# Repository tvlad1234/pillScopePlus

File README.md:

# pillScope Plus
Oscilloscope based around the STM32F401 Black Pill and a color LCD screen, meant to be used as an educational tool

## Why does it exist?
The goal of this project was to create a simple and easy to build but still very usable oscillsocope. I wanted to learn the basics of how a **digital storage oscilloscope** functions, while also ending up with something which can be used as an educational tool in the lab. A short description of how oscillscopes (and this one in particular) work can be found [here](HowItWorks.md).

## Features
* -3.3V to 3.3V input range (can be increased if using attenuator probes)
* 1MOhm input impedance
* 10uS/div minimum timebase
* 1.6 MSa/S sampling rate
* On screen measurements:
  * min/max voltage
  * peak-to-peak voltage
  * frequency
* Captured waveforms can be sent to a computer over UART and analyzed in the Tektronix TekScope app
## Required parts
### Base parts:
* STM32F401CC Black Pill development board
* 128x160 ST7735-based TFT display
* 3 pushbuttons
* LM358 dual op-amp (rail-to-rail opamps should work better in this context, but this is what I had on hand)
* 2x 68kOhm resistors (to create a 1.65V offset voltage)
* 2x 500kOhm resistors (to create the input attenuator)

### Useful, but not mandatory:
* a 5V power supply
* an opto-isolated USB UART adapter
* a BNC connector, for using proper oscilloscope probes

## Schematics
The LCD screen is connected to SPI1 (PB3-SCK, PB5-MOSI, PB12-CS, PB13-RST, PB14-DC). The buttons are connected as follows:
* PB9: Up
* PB8: Select
* PB7: Down

The output of the analog frontend is connected to ADC1_IN0, which corresponds to PA0.\
The schematic of the frontend can be found in the [frontend.pdf](frontend.pdf) file.

## Using the oscilloscope
### The UI
The Select button cycles through the different parameters, which can be adjusted using the Up and Down buttons. 

### Auto calibration
Pressing Up and Down at the same time triggers the auto-calibration function. The tip and ground clip of the probed should be coupled together while calibrating. 

### Measuring things
The frontend of the instrument makes use of a virtual ground point which is 1.65V above the real ground. Because of this, the oscilloscope and the device under test must not be sharing the same ground reference. If you need to send data to the computer while measuring a device which shares ground with the scope, you should connect the computer via an opto-isolated adapter, while powering the oscilloscope from an external source.

### Saving captured waveforms
The captured waveforms can be sent to a computer over UART.

#### CSV Output
Sending `s` (lowercase s) to the UART tells the instrument to output the captured waveform in CSV format, which is compatible with the Tektronix TekScope app.

#### Direct TekScope output 
Sending `S` (capital S) tells the scope to output raw data, which can be read by a [companion app](https://github.com/tvlad1234/tekscopeIngest). This app automatically streams the captured data to TekScope, which allows almost real-time waveform analysis on the computer.

## Code
The code can be compiled with `make`. The actual oscilloscope code of this project is located in `Core\Src`, the [scope.c](Core/Src/scope.c), [ui.c](Core/Src/ui.c) and [wave.c](Core/Src/wave.c) files. Feel free to take a look, as they're commented for ease of understanding.

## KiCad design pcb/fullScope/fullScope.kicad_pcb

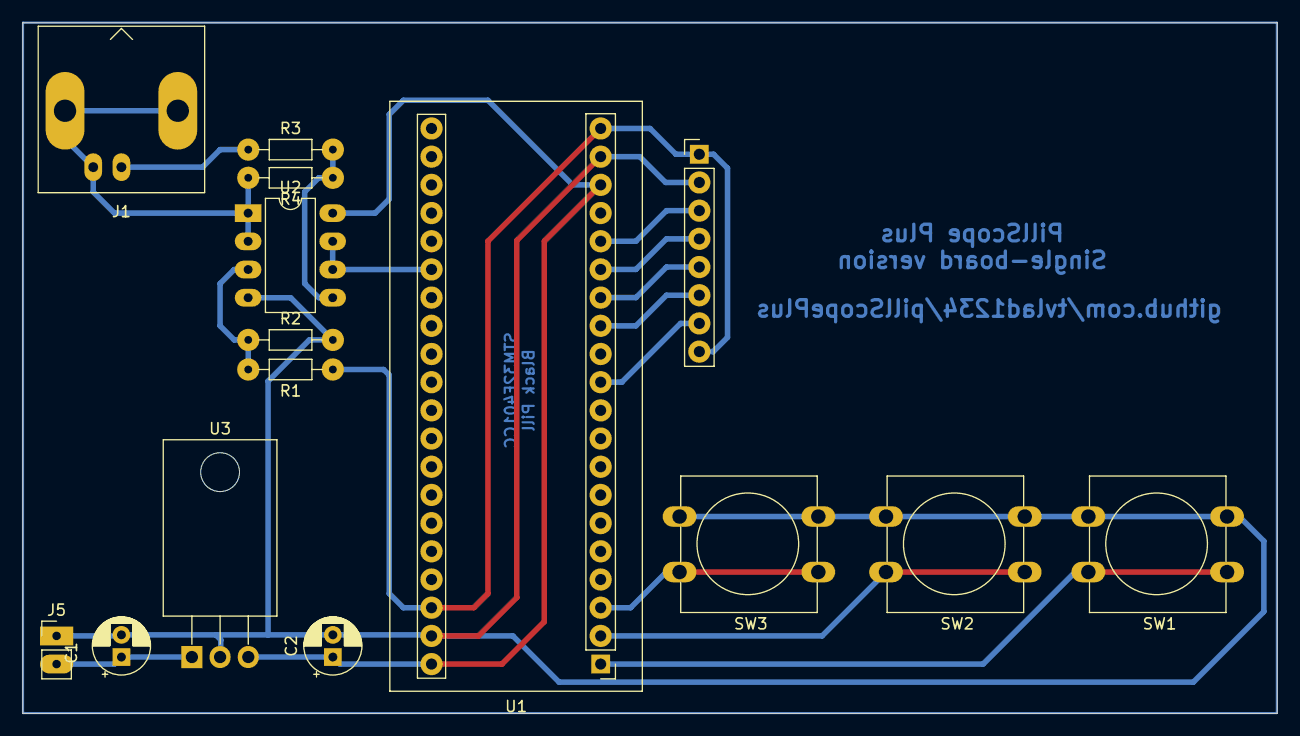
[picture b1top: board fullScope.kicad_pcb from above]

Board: 2 copper layers, 113.0 x 62.2 mm, 15 parts (0 on the bottom side), 17 nets.

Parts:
C1: 10 uF; CP_Radial_D5.0mm_P2.00mm
C2: 100 uF; CP_Radial_D5.0mm_P2.00mm
J1: IN; BNC_Amphenol_B6252HB-NPP3G-50_Horizontal
J3: LCD; PinHeader_1x08_P2.54mm_Vertical
J5: Vin; PinHeader_1x02_P2.54mm_Vertical
R1, R2: R; R_Axial_DIN0204_L3.6mm_D1.6mm_P7.62mm_Horizontal
R3, R4: 500k; R_Axial_DIN0204_L3.6mm_D1.6mm_P7.62mm_Horizontal
SW1: Btn 1; SW_PUSH-12mm
SW2: Btn 2; SW_PUSH-12mm
SW3: Btn 3; SW_PUSH-12mm
U1: F401CC; YAAJ_WeAct_BlackPill_2
U2: LM358; DIP-8_W7.62mm_LongPads
U3: LM7805; TO-220-3_Horizontal_TabDown

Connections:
+3.3V: J3.1, J3.8, R1.1, U1.20 (3V3), U1.38 (3V3)
+5V: C2.1, U1.18 (5V), U1.40 (5V), U2.8 (V+), U3.3 (VO)
+9V: C1.1, J5.2, U3.1 (VI)
BTN1: SW1.1, U1.1 (PB12)
BTN2: SW2.1, U1.2 (PB13)
BTN3: SW3.1, U1.3 (PB14)
CS: J3.3, U1.16 (PB8)
DC: J3.5, U1.14 (PB6)
FE_OUT: U1.26 (PA0), U2.6 (-), U2.7
GND: C1.2, C2.2, J3.2, J5.1, R2.2, SW1.2, SW2.2, SW3.2, U1.19 (GND), U1.39 (GND), U2.4 (V-), U3.2 (GND)
GNDS: J1.2 (Ext), R4.2, U2.1, U2.2 (-)
IN+: J1.1 (In), R3.1
MOSI: J3.6, U1.13 (PB5)
unnamed: R1.2, R2.1, U2.3 (+)
unnamed: R3.2, R4.1, U2.5 (+)
RES: J3.4, U1.15 (PB7)
SCK: J3.7, U1.11 (PB3)

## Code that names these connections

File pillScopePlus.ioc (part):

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Mcu.Name=STM32F401C(B-C)Ux
Mcu.Package=UFQFPN48
Mcu.UserName=STM32F401CCUx
PA0-WKUP.Signal=ADCx_IN0
PA10.Mode=Asynchronous
PA10.Signal=USART1_RX
PA13.Mode=Serial_Wire
PA13.Signal=SYS_JTMS-SWDIO
PA14.Mode=Serial_Wire
PA14.Signal=SYS_JTCK-SWCLK
PA9.Mode=Asynchronous
PA9.Signal=USART1_TX
PB12.GPIOParameters=GPIO_Label
PB12.GPIO_Label=ST7735_CS
PB12.Signal=GPIO_Output
PB13.GPIOParameters=GPIO_Label
PB13.GPIO_Label=ST7735_RES
PB13.Signal=GPIO_Output
PB14.GPIOParameters=GPIO_Label
PB14.GPIO_Label=ST7735_DC
PB14.Signal=GPIO_Output
PB3.Mode=TX_Only_Simplex_Unidirect_Master
PB3.Signal=SPI1_SCK
PB5.Mode=TX_Only_Simplex_Unidirect_Master
PB5.Signal=SPI1_MOSI
PB7.GPIOParameters=GPIO_PuPd,GPIO_Label
PB7.GPIO_Label=BTN1
PB7.GPIO_PuPd=GPIO_PULLUP
PB7.Signal=GPIO_Input
PB8.GPIOParameters=GPIO_PuPd,GPIO_Label
PB8.GPIO_Label=BTN2
PB8.GPIO_PuPd=GPIO_PULLUP
PB8.Signal=GPIO_Input
PB9.GPIOParameters=GPIO_PuPd,GPIO_Label
PB9.GPIO_Label=BTN3
PB9.GPIO_PuPd=GPIO_PULLUP
PB9.Signal=GPIO_Input
PC13-ANTI_TAMP.GPIOParameters=GPIO_Label
PC13-ANTI_TAMP.GPIO_Label=LED
PC13-ANTI_TAMP.Signal=GPIO_Output
PH0\ -\ OSC_IN.Mode=HSE-External-Oscillator
PH0\ -\ OSC_IN.Signal=RCC_OSC_IN
PH1\ -\ OSC_OUT.Mode=HSE-External-Oscillator
PH1\ -\ OSC_OUT.Signal=RCC_OSC_OUT
RCC.HSE_VALUE=25000000
RCC.SYSCLKFreq_VALUE=100000000
RCC.SYSCLKSource=RCC_SYSCLKSOURCE_PLLCLK
board=custom

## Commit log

2022-06-23 New UI
2022-06-23 Changed pins, better UI
2022-06-26 enable uart
2022-07-01 send csv data via uart or usb
2022-07-02 implement autocal, do sampling in separate func
2022-07-03 prevent clipping through graticule
2022-07-03 readme, changed default offset to be more accurate
2022-07-06 add raw data output, for the companion app
2022-07-10 only send half of the buffer if F is received
2022-07-13 boot logo, removed USB, increased sample rate
2022-07-13 Documentation
2023-01-25 change license, remove tekscope, ealy scpi support
2023-02-25 Add PCB files
2023-03-01 Update README.md
    Spelling
